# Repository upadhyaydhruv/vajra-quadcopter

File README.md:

# vajra-quadcopter
Custom quadcopter firmware written in STM32 HAL

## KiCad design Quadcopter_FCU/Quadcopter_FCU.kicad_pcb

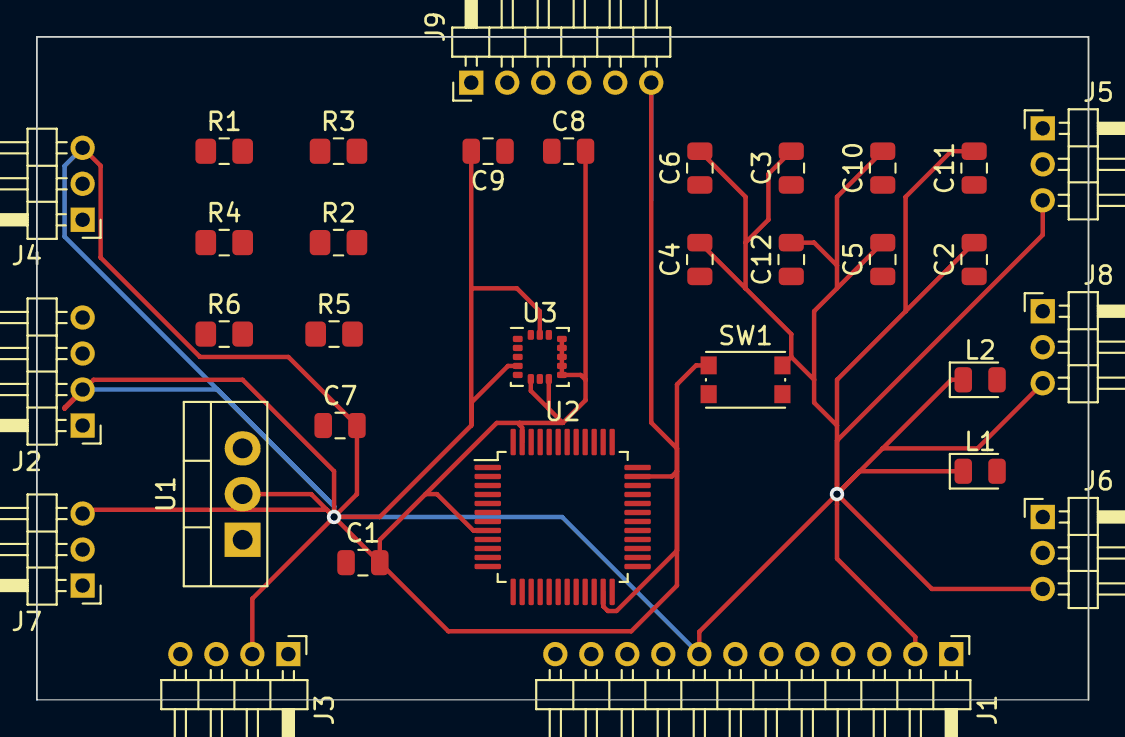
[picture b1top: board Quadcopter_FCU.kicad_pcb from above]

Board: 4 copper layers, 58.4 x 36.8 mm, 33 parts (0 on the bottom side), 21 nets.

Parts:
C1: 4u7; C_0805_2012Metric
C2, C3, C4, C5: 100n; C_0805_2012Metric
C6: 1u; C_0805_2012Metric
C7, C9, C10, C11: 0.1u; C_0805_2012Metric
C8: 100u; C_0805_2012Metric
C12: 2.2u; C_0805_2012Metric
J1: Conn_01x12_Male; PinHeader_1x12_P2.00mm_Horizontal
J2, J3: Conn_01x04_Male; PinHeader_1x04_P2.00mm_Horizontal
J4, J5, J6, J7, J8: Conn_01x03_Male; PinHeader_1x03_P2.00mm_Horizontal
J9: Conn_01x06_Male; PinHeader_1x06_P2.00mm_Horizontal
L1, L2: XZVG53W-8; LED_0805_2012Metric
R1, R2, R3, R4: 4.7k; R_0805_2012Metric_Pad1.15x1.40mm_HandSolder
R5: 5.9k; R_0805_2012Metric_Pad1.15x1.40mm_HandSolder
R6: 2.4k; R_0805_2012Metric_Pad1.15x1.40mm_HandSolder
SW1: SW_Push_Dual_x2; SW_Push_1P1T_NO_CK_KMR2
U1: LM2931-3.3_TO220; TO-220-3_Vertical
U2: STM32L151C6TxA; LQFP-48_7x7mm_P0.5mm
U3: ICM-20602; LGA-16_3x3mm_P0.5mm_LayoutBorder3x5y

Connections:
+3.3VA: C1.1, C2.1, C3.1, C4.1, C5.1, C6.1, C8.1, C11.1, C12.1, J1.1, J1.7, J2.1, J3.1, J9.5, R1.2, R2.2, R3.2, R4.2, R6.1, U1.3, U2.9, U2.24, U2.36, U2.48, U3.1, U3.5, U3.16
+5V: C7.1, J4.2, J5.2, J6.2, J7.2, J8.2, R5.1, U1.1
GND: C1.2, C2.2, C3.2, C4.2, C5.2, C6.2, C7.2, C8.2, C9.2, C10.2, C11.2, C12.2, J1.2, J1.8, J2.2, J3.2, J4.3, J5.3, J6.3, J7.3, J8.3, J9.6, L1.1, L2.1, SW1.1, U1.2, U2.8, U2.23, U2.35, U2.47, U3.4, U3.6, U3.8, U3.9, U3.10, U3.11, U3.12, U3.13, U3.15
I2C1_SCL: R1.1, U2.45, U3.2
I2C1_SDA: R2.1, U2.46, U3.3
I2C2_SCL: J2.3, R3.1, U2.21
I2C2_SDA: J2.4, R4.1, U2.22
NRST: C9.1, J9.4, SW1.2, U2.7
unnamed: C10.1, U3.14
unnamed: L1.2, R5.2
unnamed: L2.2, R6.2
PPM_INPUT: J8.1, U2.11
PWM1: J4.1, U2.40
PWM2: J5.1, U2.41
PWM3: J6.1, U2.18
PWM4: J7.1, U2.19
SWCLK: J9.2, U2.37
SWDIO: J9.1, U2.34
SWO: J9.3, U2.39
UART2_RX: J3.4, U2.12
UART2_TX: J3.3, U2.13

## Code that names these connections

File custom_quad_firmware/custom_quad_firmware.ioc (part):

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Mcu.Name=STM32F446R(C-E)Tx
Mcu.Package=LQFP64
Mcu.UserName=STM32F446RETx
PA10.GPIOParameters=GPIO_Label
PA10.GPIO_Label=PWM_3
PA10.Signal=S_TIM1_CH3
PA11.GPIOParameters=GPIO_Label
PA11.GPIO_Label=PWM_4
PA11.Signal=S_TIM1_CH4
PA13.GPIOParameters=GPIO_Label
PA13.GPIO_Label=TMS
PA13.Mode=Serial_Wire
PA13.Signal=SYS_JTMS-SWDIO
PA14.GPIOParameters=GPIO_Label
PA14.GPIO_Label=TCK
PA14.Mode=Serial_Wire
PA14.Signal=SYS_JTCK-SWCLK
PA15.GPIOParameters=GPIO_Label
PA15.GPIO_Label=PPM_IN
PA15.Signal=S_TIM2_CH1_ETR
PA2.GPIOParameters=GPIO_Label
PA2.GPIO_Label=USART_TX
PA2.Mode=Asynchronous
PA2.Signal=USART2_TX
PA3.GPIOParameters=GPIO_Label
PA3.GPIO_Label=USART_RX
PA3.Mode=Asynchronous
PA3.Signal=USART2_RX
PA5.GPIOParameters=GPIO_Label
PA5.GPIO_Label=LD2 [Green Led]
PA5.Signal=GPIO_Output
PA8.GPIOParameters=GPIO_Label
PA8.GPIO_Label=PWM_1
PA8.Signal=S_TIM1_CH1
PA9.GPIOParameters=GPIO_Label
PA9.GPIO_Label=PWM_2
PA9.Signal=S_TIM1_CH2
PB3.GPIOParameters=GPIO_Label
PB3.GPIO_Label=SWO
PB3.Signal=SYS_JTDO-SWO
PB5.Mode=SMBus-Alert-mode
PB5.Signal=I2C1_SMBA
PB6.Mode=SMBus-Alert-mode
PB6.Signal=I2C1_SCL
PB7.Mode=SMBus-Alert-mode
PB7.Signal=I2C1_SDA
PC13.GPIOParameters=GPIO_Label,GPIO_ModeDefaultEXTI
PC13.GPIO_Label=B1 [Blue PushButton]
PC13.GPIO_ModeDefaultEXTI=GPIO_MODE_IT_FALLING
PC13.Signal=GPXTI13
PC14-OSC32_IN.Mode=LSE-External-Oscillator
PC14-OSC32_IN.Signal=RCC_OSC32_IN
PC15-OSC32_OUT.Mode=LSE-External-Oscillator
PC15-OSC32_OUT.Signal=RCC_OSC32_OUT
PH0-OSC_IN.Mode=HSE-External-Oscillator
PH0-OSC_IN.Signal=RCC_OSC_IN
PH1-OSC_OUT.Mode=HSE-External-Oscillator
PH1-OSC_OUT.Signal=RCC_OSC_OUT
RCC.HSE_VALUE=8000000
RCC.SYSCLKFreq_VALUE=84000000
RCC.SYSCLKSource=RCC_SYSCLKSOURCE_PLLCLK
board=NUCLEO-F446RE
boardIOC=true

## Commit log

2021-07-23 Added files generated from ioc pin configuration
2021-12-31 Added files for the flight controller PCB design
2022-01-02 added boilerplate firmware code, removed old/outdated template
2022-01-02 completed header implementation for PWM
2022-01-03 added PWM setting functionality, and power LEDs to schematic
2022-01-05 completed timer configuration and PWM setting functionality
2022-01-05 fixed linking errors, code builds!
2022-01-16 implemented header for PPM capture
2022-02-05 associated footprints and generated netlist
2022-02-05 layed out ratsnest
2022-02-05 finished initial routing for ground plane
